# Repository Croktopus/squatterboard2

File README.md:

# squatterboard2

This is an update to the [squatterboard project](https://github.com/Croktopus/squatterboard), meant to resolve issues I have with the original. If you're not familiar with the original, the reason I made this was to make a daughterboard with a "squatter" profile than the standard set by the [Unified Daughterboard](https://github.com/ai03-2725/Unified-Daughterboard) (UDB), since I almost never have room in my cases for a daughterboard with those dimensions.

Electrically, it is compatible with the UDB's pinout, so it can work with any PCB compatible with the UDB. I honestly do not know how it compares for effectiveness because I don't have access to proper testing equipment, and I do know that the routing is not perfectly optimal (I made a couple slight compromises to fit everything a bit tighter and, I'll be honest, to keep the routing clean), but I'm confident that it is good enough (Cunningham's Law inc).

While you are welcome to use this DB as is without any modification, I am not proposing it as an alternative standard, and I encourage you to modify it to fit your needs, because that's why it was made in the first place; as a modification of the UDB concept to fit my needs.

Major changes from the original squatterboard:

* Built from scratch in KiCad 6
* Simplified the schematic & componentry
* Made it a bit squatter (loses physical compatibility, but I kinda just don't care about that, as I said above you can modify it to fit your needs, including moving some stuff around to restore physical compat)
* Reorganized libraries, added license, basically just trying to make the whole package a bit more portable so you don't get hit with errors when you download it and try to play around with it - let me know if I failed on that front, this was one of the big reasons I had for redoing this whole thing

Major changes relative to the UDB

* Size and shape (obviously)
* Optimized for JLC assembly with basic parts wherever possible (production files are included, though they haven't been tested as of writing)
* 2 M3 screws instead of 4 M2

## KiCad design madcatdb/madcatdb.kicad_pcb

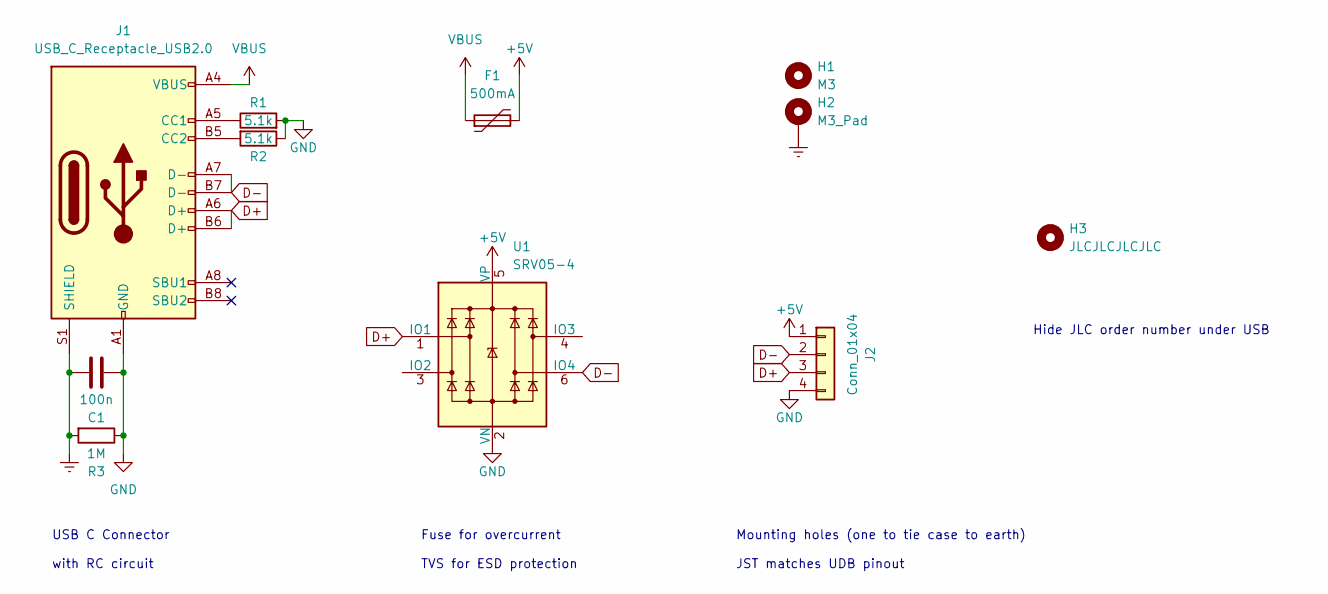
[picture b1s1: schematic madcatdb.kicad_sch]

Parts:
C1: 100n; C_1206_3216Metric
F1: 500mA; Fuse_1206_3216Metric
H1: M3; M3_Via_Hole_NC
H2: M3_Pad; M3_Via_Hole
H3: JLCJLCJLCJLC
J1: USB_C_Receptacle_USB2.0; HRO-TYPE-C-31-M-14
J2: Conn_01x04; JST_SH_SM04B-SRSS-TB-Handsoldering
R1, R2: 5.1k; R_0603_1608Metric
R3: 1M; R_1206_3216Metric
U1: SRV05-4; SOT-23-6

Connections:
+5V: F1.2, J2.1, U1.5 (VP)
D+: J1.A6 (D+), J1.B6 (D+), J2.3, U1.1 (IO1)
D-: J1.A7 (D-), J1.B7 (D-), J2.2, U1.6 (IO4)
Earth: C1.2, H2.1, J1.S1 (SHIELD), R3.2
GND: C1.1, J1.A1 (GND), J1.A12 (GND), J1.B1 (GND), J1.B12 (GND), J2.4, R1.2, R2.1, R3.1, U1.2 (VN)
unnamed: J1.A5 (CC1), R1.1
unnamed: J1.B5 (CC2), R2.2
VBUS: F1.1, J1.A4 (VBUS), J1.A9 (VBUS), J1.B4 (VBUS), J1.B9 (VBUS)

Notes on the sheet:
USB C Connector with RC circuit
Fuse for overcurrent TVS for ESD protection
Hide JLC order number under USB
Mounting holes (one to tie case to earth) JST matches UDB pinout

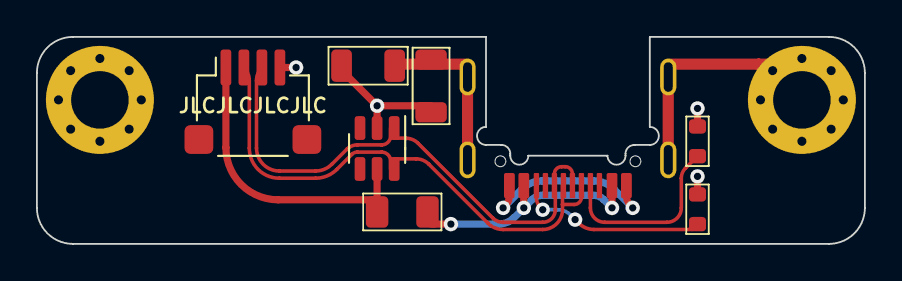
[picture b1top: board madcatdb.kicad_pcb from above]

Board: 2 copper layers, 46.0 x 11.5 mm, 11 parts (1 on the bottom side), 8 nets.

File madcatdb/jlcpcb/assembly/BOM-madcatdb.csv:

Comment,Designator,Footprint,LCSC
Conn_01x04,J2,JST_SH_SM04B-SRSS-TB-Handsoldering,C160404
USB_C_Receptacle_USB2.0,J1,USB_C_Receptacle_HRO_TYPE-C-31-M-12,C167321
1M,R3,R_1206_3216Metric,C17927
5.1k,"R1,R2",R_0603_1608Metric,C23186
100n,C1,C_1206_3216Metric,C24497
500mA,F1,Fuse_1206_3216Metric,C70076
SRV05-4,U1,SOT-23-6,C85364
M3,H1,M3_Via_Hole_NC,
M3_Pad,H2,M3_Via_Hole,
JLCJLCJLCJLC,H3,JLCJLCJLCJLC,

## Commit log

2022-03-25 started kicad project
2022-03-26 done (lol)
2022-03-26 prod files
2022-03-28 generated prod files
2022-03-28 Update kicad-custom-libs
2022-03-28 added generic squatterboard2 version
2022-03-28 update submodules
2022-03-28 Rename madcatdb.md to readme.md
2022-04-07 update libs
2022-04-07 proto ordered
2022-06-27 updated madcat to mid mount
2022-09-16 backup
